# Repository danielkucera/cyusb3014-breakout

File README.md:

View this project on [CADLAB.io](https://cadlab.io/project/23305). 

# Cypress FX3 CYUSB3014 breakout board

## Hardware

This design is a copy of QM Tech board: https://github.com/ChinaQMTECH/QM_CYUSB3014_USB3.0

You can find the most recent schematic in releases https://github.com/danielkucera/cyusb3014-breakout/releases

## Software

For quick testing of the board you can use the SPI image and python script from folder [software](/software)

These are my results for bulk loop test:

## I want one

Contact me in some way, I have some spare boards, I can send you a bare board or an assembled one for some small donation.

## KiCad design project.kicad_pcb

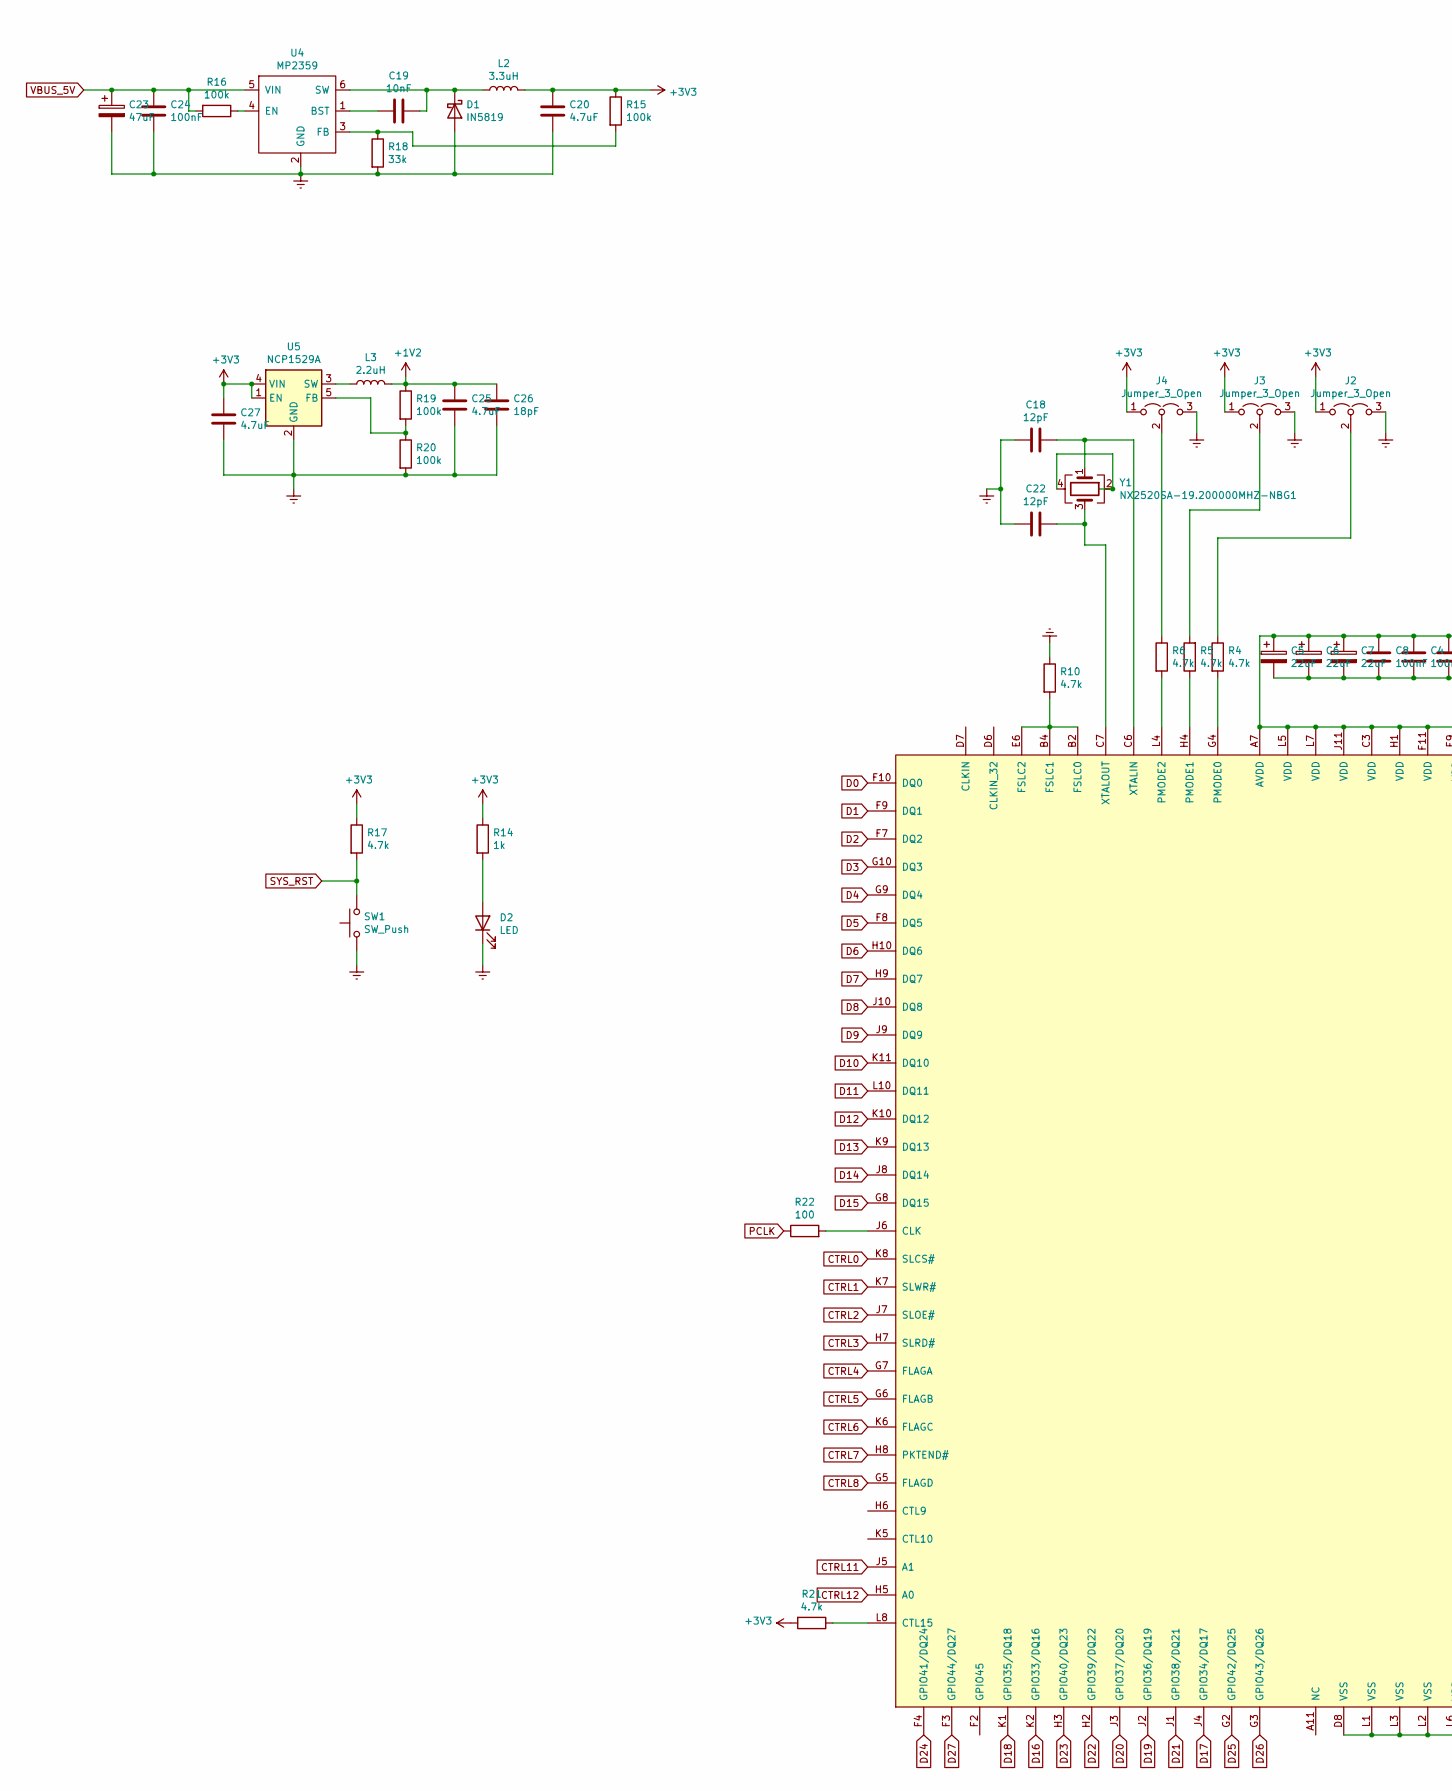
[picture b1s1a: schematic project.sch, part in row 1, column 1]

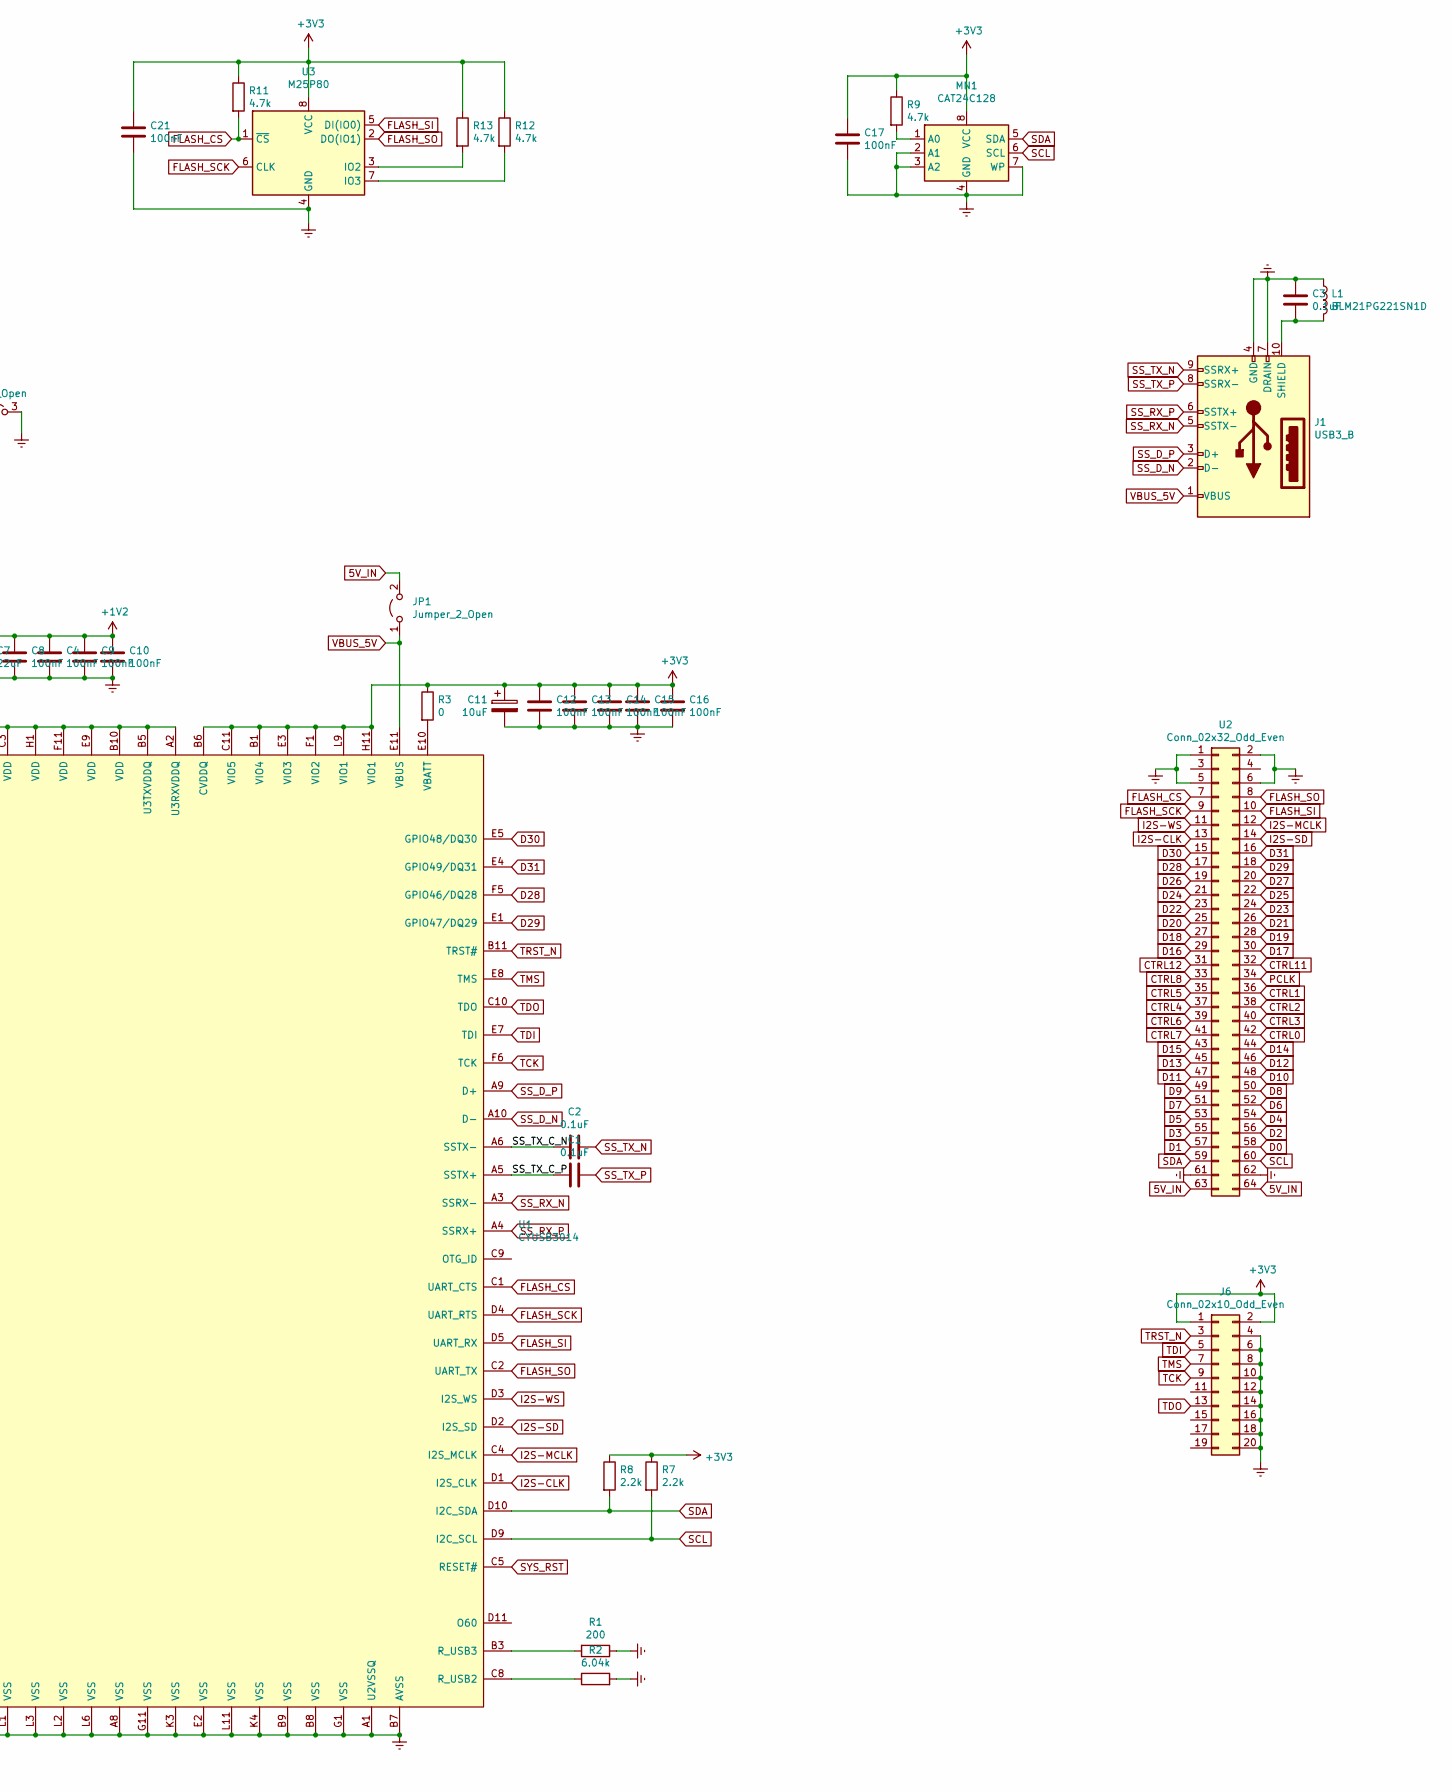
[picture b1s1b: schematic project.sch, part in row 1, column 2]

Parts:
C1, C2: 0.1uF; C_0402_1005Metric
C3: 0.1uF; C_0603_1608Metric
C4, C8, C9, C10, C12, C13, C14, C15, C16, C17, C21, C24: 100nF; C_0603_1608Metric
C5, C6, C7: 22uF; C_0805_2012Metric
C11: 10uF; C_0805_2012Metric
C18, C22: 12pF; C_0603_1608Metric
C19: 10nF; C_0603_1608Metric
C20, C25, C27: 4.7uF; C_0805_2012Metric
C23: 47uF; CP_Elec_6.3x5.8
C26: 18pF; C_0603_1608Metric
D1: IN5819; D_SMB
D2: LED; LED_0805_2012Metric
J1: USB3_B; USB_A_Female_AU-Y1006-3
J2, J3, J4: Jumper_3_Open; PinHeader_1x03_P2.54mm_Vertical
J6: Conn_02x10_Odd_Even; PinHeader_2x10_P2.54mm_Vertical
JP1: Jumper_2_Open; PinHeader_1x02_P2.54mm_Vertical
L1: BLM21PG221SN1D; L_1210_3225Metric_Pad1.42x2.65mm_HandSolder
L2: 3.3uH; L_6.3x6.3_H3
L3: 2.2uH; L_1210_3225Metric_Pad1.42x2.65mm_HandSolder
MN1: CAT24C128; SOIC-8_3.9x4.9mm_P1.27mm
R1: 200; R_0603_1608Metric
R2: 6.04k; R_0603_1608Metric
R3: 0; R_0603_1608Metric
R4, R5, R6, R9, R10, R11, R12, R13, R17, R21: 4.7k; R_0603_1608Metric
R7, R8: 2.2k; R_0603_1608Metric
R14: 1k; R_0603_1608Metric
R15, R16, R19, R20: 100k; R_0603_1608Metric
R18: 33k; R_0603_1608Metric
R22: 100; R_0603_1608Metric
SW1: SW_Push; SW_DIP_SPSTx01_Slide_6.7x4.1mm_W6.73mm_P2.54mm_LowProfile_J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
U1: CYUSB3014; TFBGA-121_10x10mm_Layout11x11_P0.8mm; Voltage _; Tolerance _
U2: Conn_02x32_Odd_Even; PinSocket_2x32_P2.54mm_Vertical
U3: M25P80; SOIC-8_5.23x5.23mm_P1.27mm
U4: MP2359; TSOT-23-6
U5: NCP1529A; SOT-23-5
Y1: NX2520SA-19.200000MHZ-NBG1; Crystal_SMD_3225-4Pin_3.2x2.5mm

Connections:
5V_IN: JP1.2 (B), U2.63, U2.64
+1V2: C4.1, C5.1, C6.1, C7.1, C8.1, C9.1, C10.1, C25.1, C26.1, L3.2, R19.1, U1.A2 (U3RXVDDQ), U1.A7 (AVDD), U1.B5 (U3TXVDDQ), U1.B10 (VDD), U1.C3 (VDD), U1.E9 (VDD), U1.F11 (VDD), U1.H1 (VDD), U1.J11 (VDD), U1.L5 (VDD), U1.L7 (VDD)
+3V3: C11.1, C12.1, C13.1, C14.1, C15.1, C16.1, C17.1, C20.1, C21.1, C27.1, J2.1 (A), J3.1 (A), J4.1 (A), J6.1, J6.2, L2.2, MN1.8 (VCC), R3.1, R7.1, R8.1, R9.1, R11.1, R12.1, R13.1, R14.1, R15.1, R17.1, R21.2, U1.B1 (VIO4), U1.B6 (CVDDQ), U1.C11 (VIO5), U1.E3 (VIO3), U1.F1 (VIO2), U1.H11 (VIO1), U1.L9 (VIO1), U3.8 (VCC), U5.1 (EN), U5.4 (VIN)
/SS_TX_C_N: C2.1, U1.A6 (SSTX-)
/SS_TX_C_P: C1.2, U1.A5 (SSTX+)
CTRL0: U1.K8 (SLCS#), U2.42
CTRL1: U1.K7 (SLWR#), U2.36
CTRL2: U1.J7 (SLOE#), U2.38
CTRL3: U1.H7 (SLRD#), U2.40
CTRL4: U1.G7 (FLAGA), U2.37
CTRL5: U1.G6 (FLAGB), U2.35
CTRL6: U1.K6 (FLAGC), U2.39
CTRL7: U1.H8 (PKTEND#), U2.41
CTRL8: U1.G5 (FLAGD), U2.33
CTRL11: U1.J5 (A1), U2.32
CTRL12: U1.H5 (A0), U2.31
D0: U1.F10 (DQ0), U2.58
D1: U1.F9 (DQ1), U2.57
D2: U1.F7 (DQ2), U2.56
D3: U1.G10 (DQ3), U2.55
D4: U1.G9 (DQ4), U2.54
D5: U1.F8 (DQ5), U2.53
D6: U1.H10 (DQ6), U2.52
D7: U1.H9 (DQ7), U2.51
D8: U1.J10 (DQ8), U2.50
D9: U1.J9 (DQ9), U2.49
D10: U1.K11 (DQ10), U2.48
D11: U1.L10 (DQ11), U2.47
D12: U1.K10 (DQ12), U2.46
D13: U1.K9 (DQ13), U2.45
D14: U1.J8 (DQ14), U2.44
D15: U1.G8 (DQ15), U2.43
D16: U1.K2 (GPIO33/DQ16), U2.29
D17: U1.J4 (GPIO34/DQ17), U2.30
D18: U1.K1 (GPIO35/DQ18), U2.27
D19: U1.J2 (GPIO36/DQ19), U2.28
D20: U1.J3 (GPIO37/DQ20), U2.25
D21: U1.J1 (GPIO38/DQ21), U2.26
D22: U1.H2 (GPIO39/DQ22), U2.23
D23: U1.H3 (GPIO40/DQ23), U2.24
D24: U1.F4 (GPIO41/DQ24), U2.21
D25: U1.G2 (GPIO42/DQ25), U2.22
D26: U1.G3 (GPIO43/DQ26), U2.19
D27: U1.F3 (GPIO44/DQ27), U2.20
D28: U1.F5 (GPIO46/DQ28), U2.17
D29: U1.E1 (GPIO47/DQ29), U2.18
D30: U1.E5 (GPIO48/DQ30), U2.15
D31: U1.E4 (GPIO49/DQ31), U2.16
Earth: C3.1, C4.2, C5.2, C6.2, C7.2, C8.2, C9.2, C10.2, C11.2, C12.2, C13.2, C14.2, C15.2, C16.2, C17.2, C18.2, C20.2, C21.2, C22.2, C23.2, C24.2, C25.2, C26.2, C27.2, D1.2 (A), D2.1 (K), J1.4 (GND), J1.7 (DRAIN), J2.3 (B), J3.3 (B), J4.3 (B), J6.4, J6.6, J6.8, J6.10, J6.12, J6.14, J6.16, J6.18, J6.20, L1.1, MN1.2 (A1), MN1.3 (A2), MN1.4 (GND), MN1.7 (WP), R1.1, R2.2, R10.1, R18.2, R20.2, SW1.1, U1.A1 (U2VSSQ), U1.A8 (VSS), U1.B7 (AVSS), U1.B8 (VSS), U1.B9 (VSS), U1.D8 (VSS), U1.E2 (VSS), U1.G1 (VSS), U1.G11 (VSS), U1.K3 (VSS), U1.K4 (VSS), U1.L1 (VSS), U1.L2 (VSS), U1.L3 (VSS), U1.L6 (VSS), U1.L11 (VSS), U2.1, U2.2, U2.5, U2.6, U2.61, U2.62, U3.4 (GND), U4.2 (GND), U5.2 (GND)
FLASH_CS: R11.2, U1.C1 (UART_CTS), U2.7, U3.1 (~CS)
FLASH_SCK: U1.D4 (UART_RTS), U2.9, U3.6 (CLK)
FLASH_SI: U1.D5 (UART_RX), U2.10, U3.5 (DI(IO0))
FLASH_SO: U1.C2 (UART_TX), U2.8, U3.2 (DO(IO1))
I2S-CLK: U1.D1 (I2S_CLK), U2.13
I2S-MCLK: U1.C4 (I2S_MCLK), U2.12
I2S-SD: U1.D2 (I2S_SD), U2.14
I2S-WS: U1.D3 (I2S_WS), U2.11
unnamed: C3.2, J1.10 (SHIELD), L1.2
unnamed: C18.1, U1.C6 (XTALIN), Y1.1
unnamed: C19.1, D1.1 (K), L2.1, U4.6 (SW)
unnamed: C19.2, U4.1 (BST)
unnamed: C22.1, U1.C7 (XTALOUT), Y1.3
unnamed: D2.2 (A), R14.2
unnamed: J2.2 (C), R4.1
unnamed: J3.2 (C), R5.2
unnamed: J4.2 (C), R6.1
unnamed: L3.1, U5.3 (SW)
unnamed: MN1.1 (A0), R9.2
unnamed: R1.2, U1.B3 (R_USB3)
unnamed: R2.1, U1.C8 (R_USB2)
unnamed: R3.2, U1.E10 (VBATT)
unnamed: R4.2, U1.G4 (PMODE0)
unnamed: R5.1, U1.H4 (PMODE1)
unnamed: R6.2, U1.L4 (PMODE2)
unnamed: R10.2, U1.B2 (FSLC0), U1.B4 (FSLC1), U1.E6 (FSLC2)
unnamed: R12.2, U3.7 (IO3)
unnamed: R13.2, U3.3 (IO2)
unnamed: R15.2, R18.1, U4.3 (FB)
unnamed: R16.1, U4.4 (EN)
unnamed: R19.2, R20.1, U5.5 (FB)
unnamed: R21.1, U1.L8 (CTL15)
unnamed: R22.2, U1.J6 (CLK)
unnamed: Y1.2, Y1.4
PCLK: R22.1, U2.34
SCL: MN1.6 (SCL), R7.2, U1.D9 (I2C_SCL), U2.60
SDA: MN1.5 (SDA), R8.2, U1.D10 (I2C_SDA), U2.59
SS_D_N: J1.2 (D-), U1.A10 (D-)
SS_D_P: J1.3 (D+), U1.A9 (D+)
SS_RX_N: J1.5 (SSTX-), U1.A3 (SSRX-)
SS_RX_P: J1.6 (SSTX+), U1.A4 (SSRX+)
SS_TX_N: C2.2, J1.9 (SSRX+)
SS_TX_P: C1.1, J1.8 (SSRX-)
SYS_RST: R17.2, SW1.2, U1.C5 (RESET#)
TCK: J6.9, U1.F6 (TCK)
TDI: J6.5, U1.E7 (TDI)
TDO: J6.13, U1.C10 (TDO)
TMS: J6.7, U1.E8 (TMS)
TRST_N: J6.3, U1.B11 (TRST#)
VBUS_5V: C23.1, C24.1, J1.1 (VBUS), JP1.1 (A), R16.2, U1.E11 (VBUS), U4.5 (VIN)

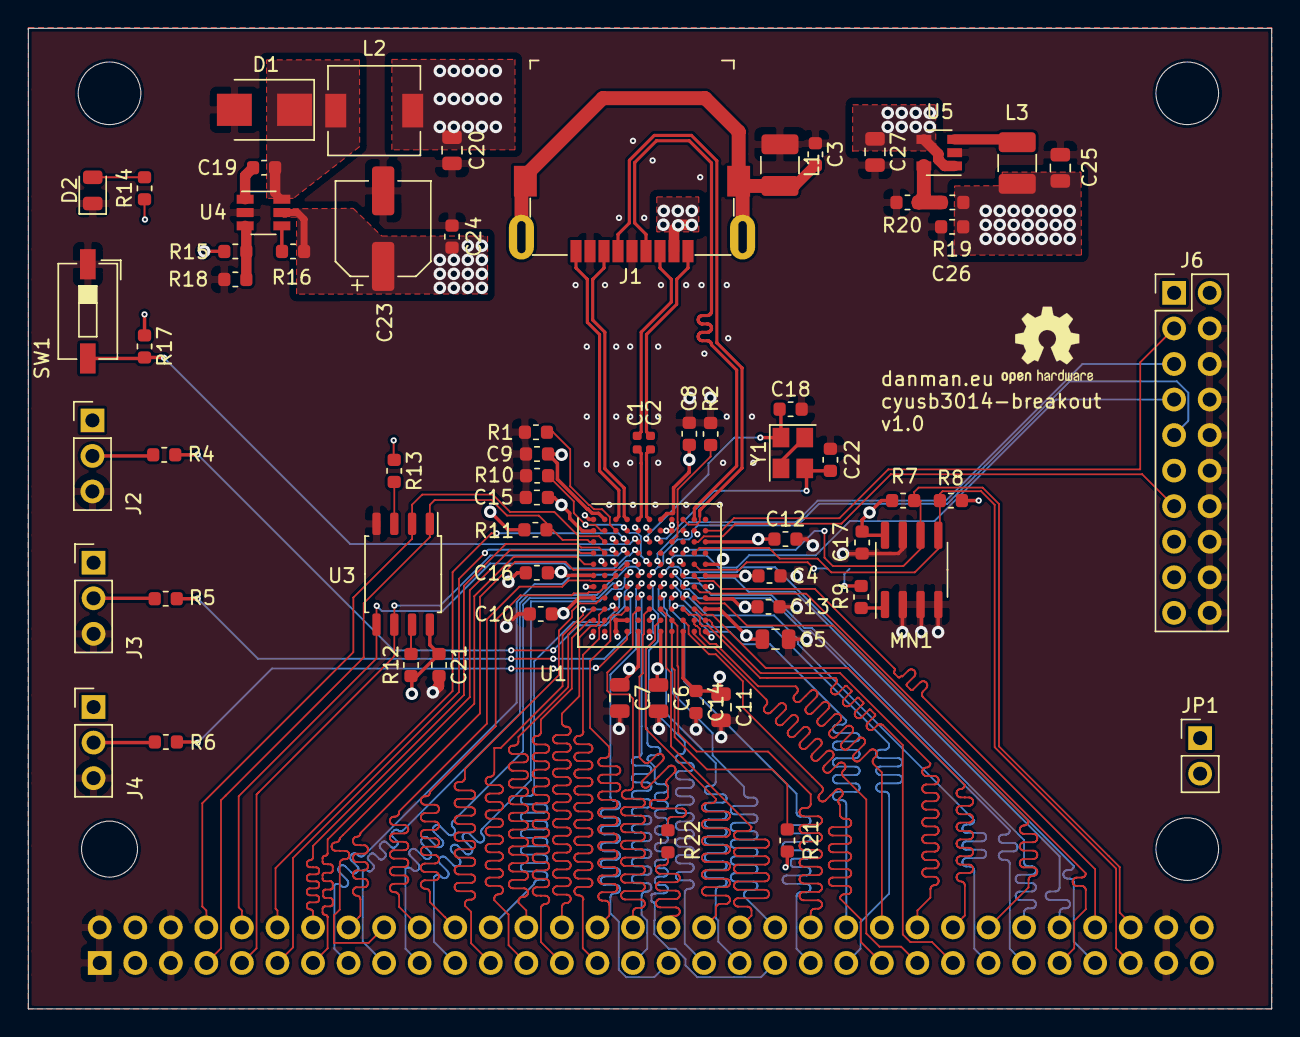
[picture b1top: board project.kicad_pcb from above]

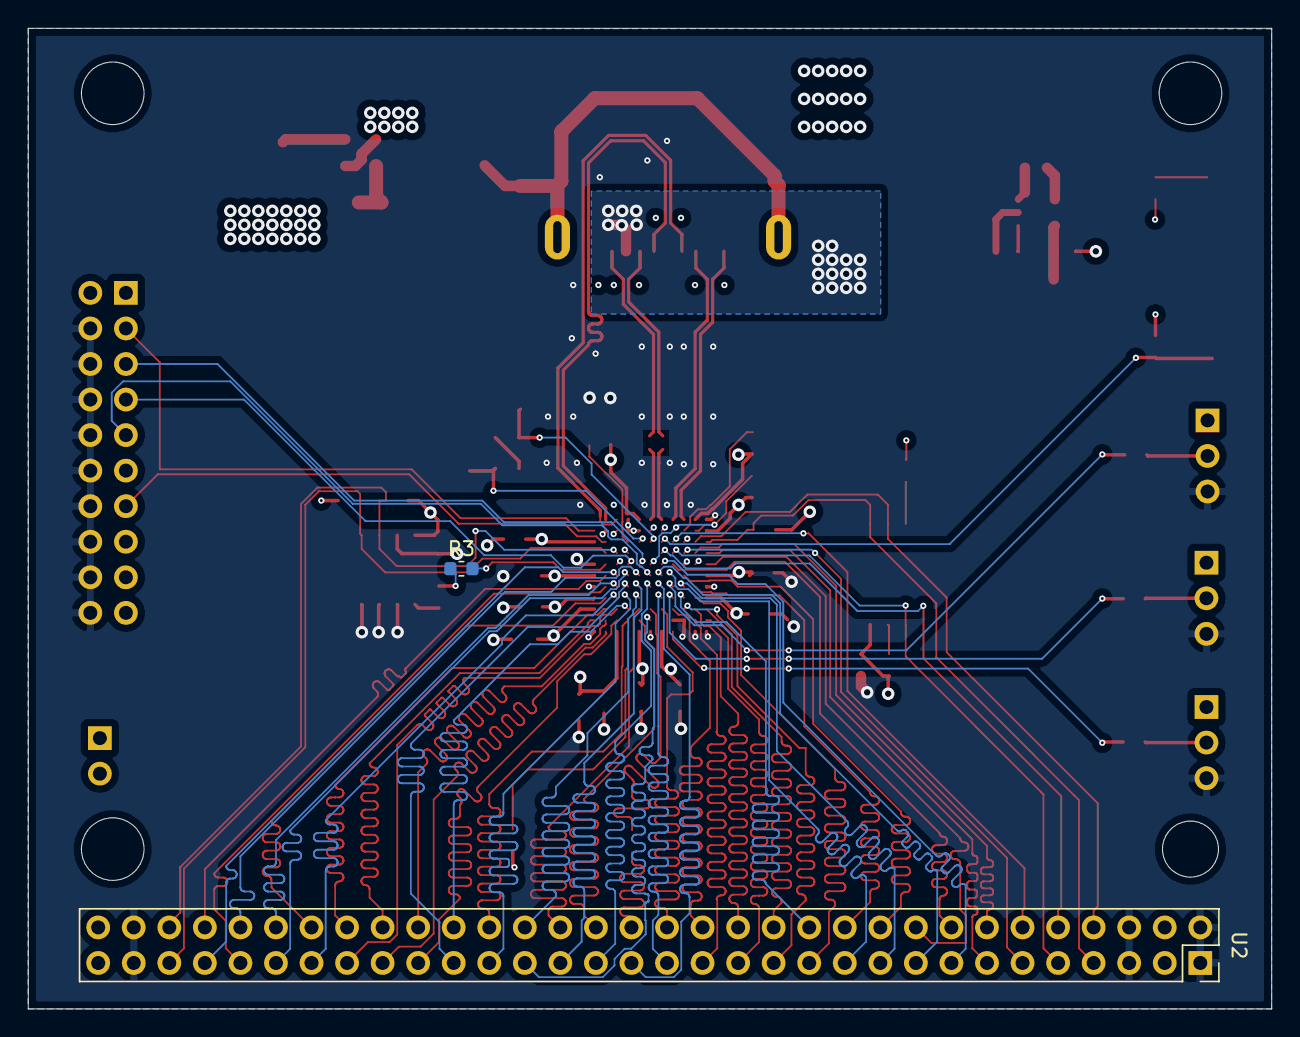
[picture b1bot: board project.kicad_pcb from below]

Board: 4 copper layers, 88.8 x 70.1 mm, 68 parts (2 on the bottom side), 99 nets.

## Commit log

2020-05-21 initial commit - top layer routed
2020-05-23 everything routed
2020-05-23 final with silk and holes
2020-05-23 5v on pwr plane
2020-05-23 added logo
2020-06-13 added manufactured board photo
2020-06-13 added travis
2020-08-08 added images and loopback test
2020-08-08 added loop image from cypress samples
2020-09-13 Backlink to CADLAB.io has been added.
